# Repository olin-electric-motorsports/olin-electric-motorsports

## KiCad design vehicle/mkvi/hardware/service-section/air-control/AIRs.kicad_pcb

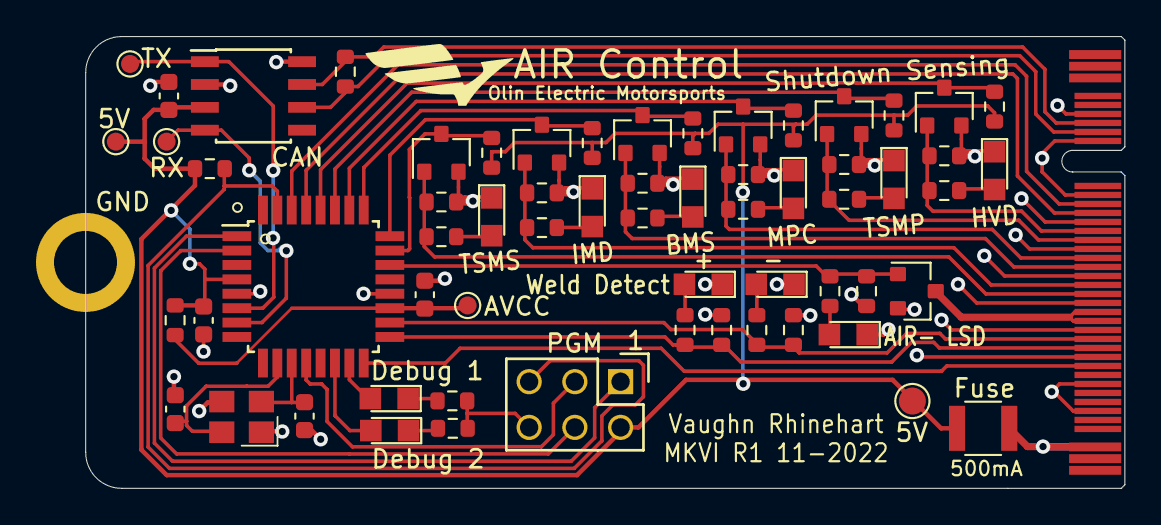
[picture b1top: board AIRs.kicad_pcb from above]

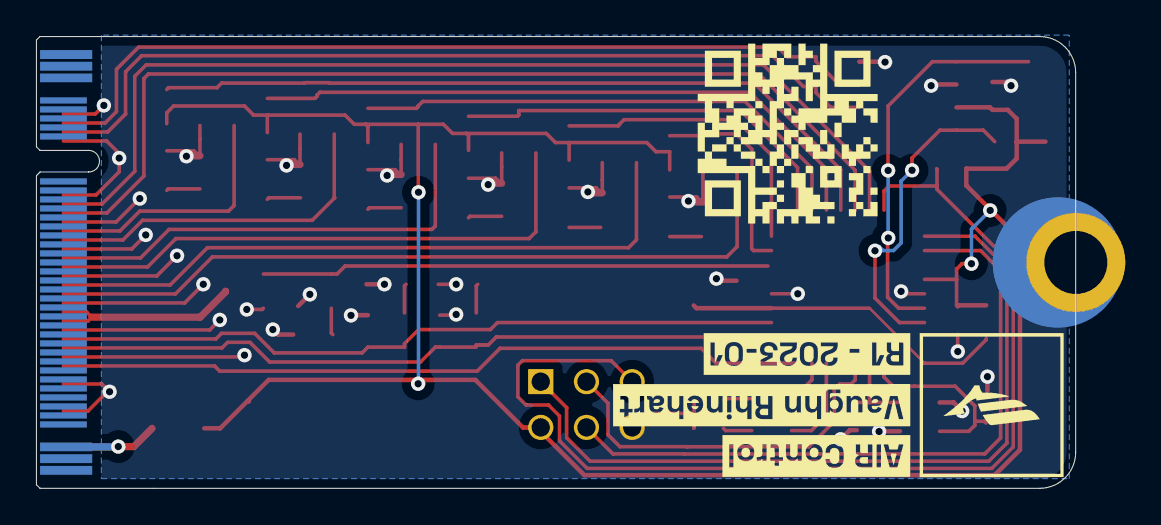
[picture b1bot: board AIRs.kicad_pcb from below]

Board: 2 copper layers, 57.7 x 25.1 mm, 68 parts (4 on the bottom side), 46 nets.

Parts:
C1, C7: 0.1uF; C_0603
C2: C_100pF; C_0603
C3, C4: C_30pF; C_0603
D2, D3, D4: LED_WHITE; CHIPLED_0805
D5, D6, D7, D8, D9, D10: LED_BLUE; CHIPLED_0805
F1: F_500mA_16V; Fuse_1210
J1: Programming; Pin_Header_Straight_2x03
J2: M.2 Edge Connector; Automotive_M.2_Edge_Connector
PD1, PD2: LED_WHITE; CHIPLED_0805
Q1, Q2, Q3, Q4, Q5, Q6, Q7: SSM3K333R; SOT-23F
QR*****: hw.oem.to/6_AIR-CNTL_1; QR_6_AIR-CNTL_1
R1: R_100; R_0603
R2, R3, R6, R7, R8: 1KR; R_0603
R4, R9, R10, R11, R12, R15, R18, R21, R24, R27: R_10K; R_0603
R13, R16, R19, R22, R25, R28: R_100K; R_0603
R14, R17, R20, R23, R26, R29: 3KR; R_0603
R30: R_120_DNP; R_0603
TP1, TP2, TP3, TP4: Test_Point_SMD; TestPoint_Pad_D1.0mm
TP5: Test_Point_SMD; TestPoint_Pad_D1.5mm
TP7: Test_Point_SMD; M.2_Mount
U1: ATMEGA16M1; TQFP-32_7x7mm_Pitch0.8mm
U2: MAX33011EASA; SOIC-8_3.9x4.9mm_Pitch1.27mm_OEM
Y1: Crystal_16MHz_18pF; Crystal_TXC7M
kibuzzard-63BF4696: G***; kibuzzard-63BF4696
kibuzzard-63D83D19: G***; kibuzzard-63D83D19
kibuzzard-63D83D27: G***; kibuzzard-63D83D27

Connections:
+5V: C1.1, C7.1, F1.1, J1.2, R1.1, R4.2, R12.1, R15.1, R18.1, R21.1, R24.1, R27.1, TP1.1, TP5.1, U1.4 (VCC), U2.3 (VDD)
/AIR+_WELD_DETECT: J2.28, R6.1, R9.1, U1.17 ((PCINT12/ADC8/ACMPN3/AMP1-)PC4)
/AIR-_LSD: Q1.1 (G), R7.1, R10.1, U1.22 ((PCINT14/ADC10/ACMP1)PC6)
/AIR-_LSD_OUT: J2.24, J2.25, Q1.3 (D)
/AIR-_WELD_DETECT: J2.27, R8.1, R11.1, U1.18 ((PCINT13/ADC9/ACMP3/AMP1+)PC5)
/CAN Tcvr./CAN RX: TP4.1, U1.7 ((PCINT11/T1/ICP1B/RXCAN)PC3), U2.4 (RXD)
/CAN Tcvr./CAN TX: TP3.1, U1.6 ((PCINT10/T0/TXCAN)PC2), U2.1 (TXD)
/CAN_+: J2.7, R30.1, U2.7 (CANH)
/CAN_-: J2.8, R30.2, U2.6 (CANL)
/IMD_PWM: J2.12, U1.30 ((PCINT8/INT3/PSCOUT1A)PC0)
/IMD_STATUS: J2.13, U1.29 ((PCINT16/PSCOUT0A)PD0)
/MISO: J1.1, U1.1 ((PCINT18/PSCIN2/OC1A/MISO_A)PD2)
/MOSI: J1.4, U1.2 ((PCINT19/TXD/TXLIN/OC0A/~SS/MOSI_A)PD3)
/PRECHARGE: J2.30, U1.16 ((PCINT2/ADC5/INT1/ACMPN0)PB2)
/RESET: J1.5, R4.1, U1.31 ((PCINT24/OCD/~RESET)PE0)
/SCK: J1.3, U1.12 ((PCINT20/ADC1/RXD/RXLIN/ICP1A/SCK_A)PD4)
/SHDN_SENSE_BMS: Q5.3 (D), R21.2, U1.25 ((PCINT15/D2A/AMP2+)PC7)
/SHDN_SENSE_BMS_12V: J2.19, Q5.1 (G), R22.1, R23.1
/SHDN_SENSE_HVD: Q2.3 (D), R12.2, U1.28 ((PCINT7/ADC4/SCK/PSCOUT0B)PB7)
/SHDN_SENSE_HVD_12V: J2.15, Q2.1 (G), R13.1, R14.1
/SHDN_SENSE_IMD: Q6.3 (D), R24.2, U1.24 ((PCINT4/AMP0+)PB4)
/SHDN_SENSE_IMD_12V: J2.21, Q6.1 (G), R25.1, R26.1
/SHDN_SENSE_MPC: Q4.3 (D), R18.2, U1.26 ((PCINT5/ADC6/INT2/ACMPN1/AMP2-)PB5)
/SHDN_SENSE_MPC_12V: J2.18, Q4.1 (G), R19.1, R20.1
/SHDN_SENSE_TSMP: Q3.3 (D), R15.2, U1.27 ((PCINT6/ADC7/PSCOUT1B)PB6)
/SHDN_SENSE_TSMP_12V: J2.16, Q3.1 (G), R16.1, R17.1
/SHDN_SENSE_TSMS: Q7.3 (D), R27.2, U1.23 ((PCINT3/AMP0-)PB3)
/SHDN_SENSE_TSMS_12V: J2.22, Q7.1 (G), R28.1, R29.1
GND: C1.2, C2.2, C3.2, C4.2, C7.2, D2.1 (K), D3.1 (K), D4.1 (K), D5.1 (K), D6.1 (K), D7.1 (K), D8.1 (K), D9.1 (K), D10.1 (K), J1.6, J2.6, J2.9, J2.11, J2.14, J2.17, J2.20, J2.23, J2.26, J2.29, J2.32, J2.35, Q1.2 (S), Q2.2 (S), Q3.2 (S), Q4.2 (S), Q5.2 (S), Q6.2 (S), Q7.2 (S), R2.2, R3.2, R9.2, R10.2, R11.2, R13.2, R16.2, R19.2, R22.2, R25.2, R28.2, TP7.1, U1.5 (GND), U1.20 (AGND), U2.2 (VSS), U2.8 (STBY), Y1.2, Y1.4
unnamed: C2.1, R1.2, TP2.1, U1.19 (AVCC)
unnamed: C3.1, U1.11 ((PCINT26/ADC0/XTAL2)PE2), Y1.1
unnamed: C4.1, U1.10 ((PCINT25/OC0B/XTAL1)PE1), Y1.3
unnamed: D2.2 (A), R6.2
unnamed: D3.2 (A), R7.2
unnamed: D4.2 (A), R8.2
unnamed: D5.2 (A), R14.2
unnamed: D6.2 (A), R17.2
unnamed: D7.2 (A), R20.2
unnamed: D8.2 (A), R23.2
unnamed: D9.2 (A), R26.2
unnamed: D10.2 (A), R29.2
unnamed: F1.2, J2.P38
unnamed: PD1.1 (K), R2.1
unnamed: PD1.2 (A), U1.14 ((PCINT22/ADC3/INT0/ACMPN2)PD6)
unnamed: PD2.1 (K), R3.1
unnamed: PD2.2 (A), U1.15 ((PCINT23/ACMP0)PD7)

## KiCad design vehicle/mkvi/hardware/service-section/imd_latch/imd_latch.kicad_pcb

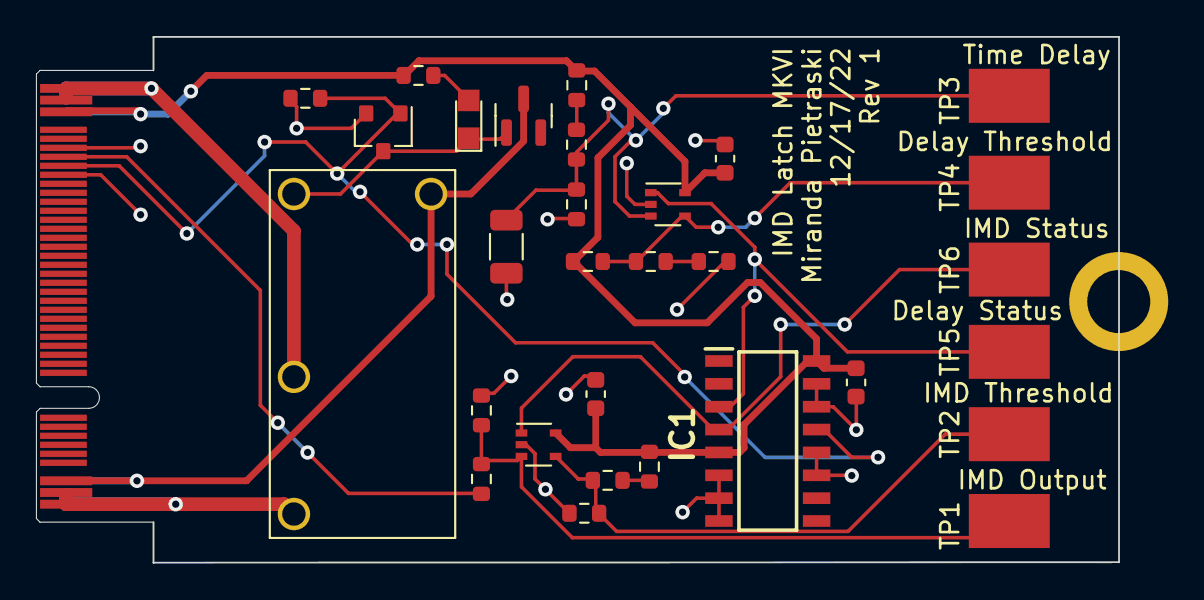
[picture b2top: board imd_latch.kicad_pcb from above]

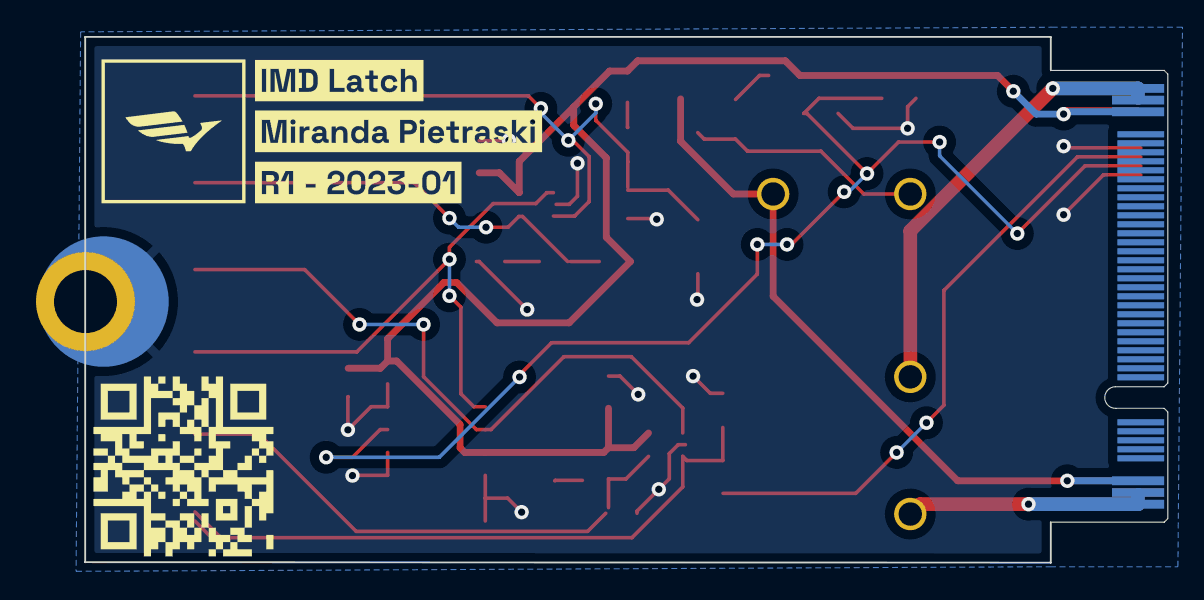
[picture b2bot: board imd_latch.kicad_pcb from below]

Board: 2 copper layers, 60.1 x 29.2 mm, 36 parts (4 on the bottom side), 18 nets.

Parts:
C1: C_22uF; C_1206_3216Metric
C2, C3, C4: 0.1uF; C_0603
D1: BAS40; SOT-23
D2: LED_WHITE; CHIPLED_0805
H1: M.2_MountingHole; M.2_Mount
IC1: CD4044BDR; SOIC127P600X175-16N
J2: Automotive_M.2_Edge_Connector
K1: G5Q-1A4-DC12; Relay_SPST_OMRON-G5Q-1A4_OEM
Q1: SSM3K333R; SOT-23F
QR*****: hw.oem.to/6_IMD-LATCH_1; QR_6_IMD-LATCH_1
R1, R3, R4, R6, R7, R11: R_100K; R_0603
R2: R_71.5k; R_0603
R5: R_120K; R_0603
R8: R_3K; R_0603
R9, R13: R_1K; R_0603
R10: R_1.82M; R_0603
R12: R_604K; R_0603
TP1, TP2, TP3, TP4, TP5, TP6: Test_Point_SMD
U1, U2: MCP6001; SOT-353_SC-70-5
kibuzzard-63BF4696: G***; kibuzzard-63BF4696
kibuzzard-63D83E83: G***; kibuzzard-63D83E83
kibuzzard-63D83E95: G***; kibuzzard-63D83E95

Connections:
+5V: C2.1, C3.1, C4.1, IC1.5 (ENABLE), IC1.16 (VDD), J2.P38, R1.1, R2.2, R3.1, R13.1, U1.5 (V+), U2.5 (V+)
+BATT: D1.3 (K), J2.P3, K1.5
/IMD_OUTPUT: J2.34, R8.1
/IMD_STATUS: IC1.13 (Q1), J2.33, Q1.1 (G), R12.1
/IMD_STATUS_OUTPUT: IC1.4 (RI), TP6.1, U1.1
/SHDN_IN: J2.P1, J2.P2, K1.3
/SHDN_OUT: J2.P39, J2.P40, K1.2
/TIME_DELAY: IC1.3 (SI), TP5.1, U2.1
GND: C1.2, C2.2, C3.2, C4.2, H1.1, IC1.6 (R2), IC1.7 (S2), IC1.8 (VSS), IC1.11 (S3), IC1.12 (R3), IC1.14 (R4), IC1.15 (S4), J2.32, J2.35, Q1.2 (S), R6.1, R7.1, R9.2, R10.2, R12.2, U1.2 (V-), U2.2 (V-)
unnamed: C1.1, R5.2, R10.1, TP3.1, U2.3 (+)
unnamed: D1.1 (A), D2.1 (K), K1.1, Q1.3 (D)
unnamed: D2.2 (A), R13.2
unnamed: R1.2, R4.2, TP4.1, U2.4 (-)
unnamed: R2.1, R5.1
unnamed: R4.1, R7.2
unnamed: R8.2, R9.1, TP1.1, U1.3 (+)
unnamed: R3.2, R11.1
unnamed: R6.2, R11.2, TP2.1, U1.4 (-)

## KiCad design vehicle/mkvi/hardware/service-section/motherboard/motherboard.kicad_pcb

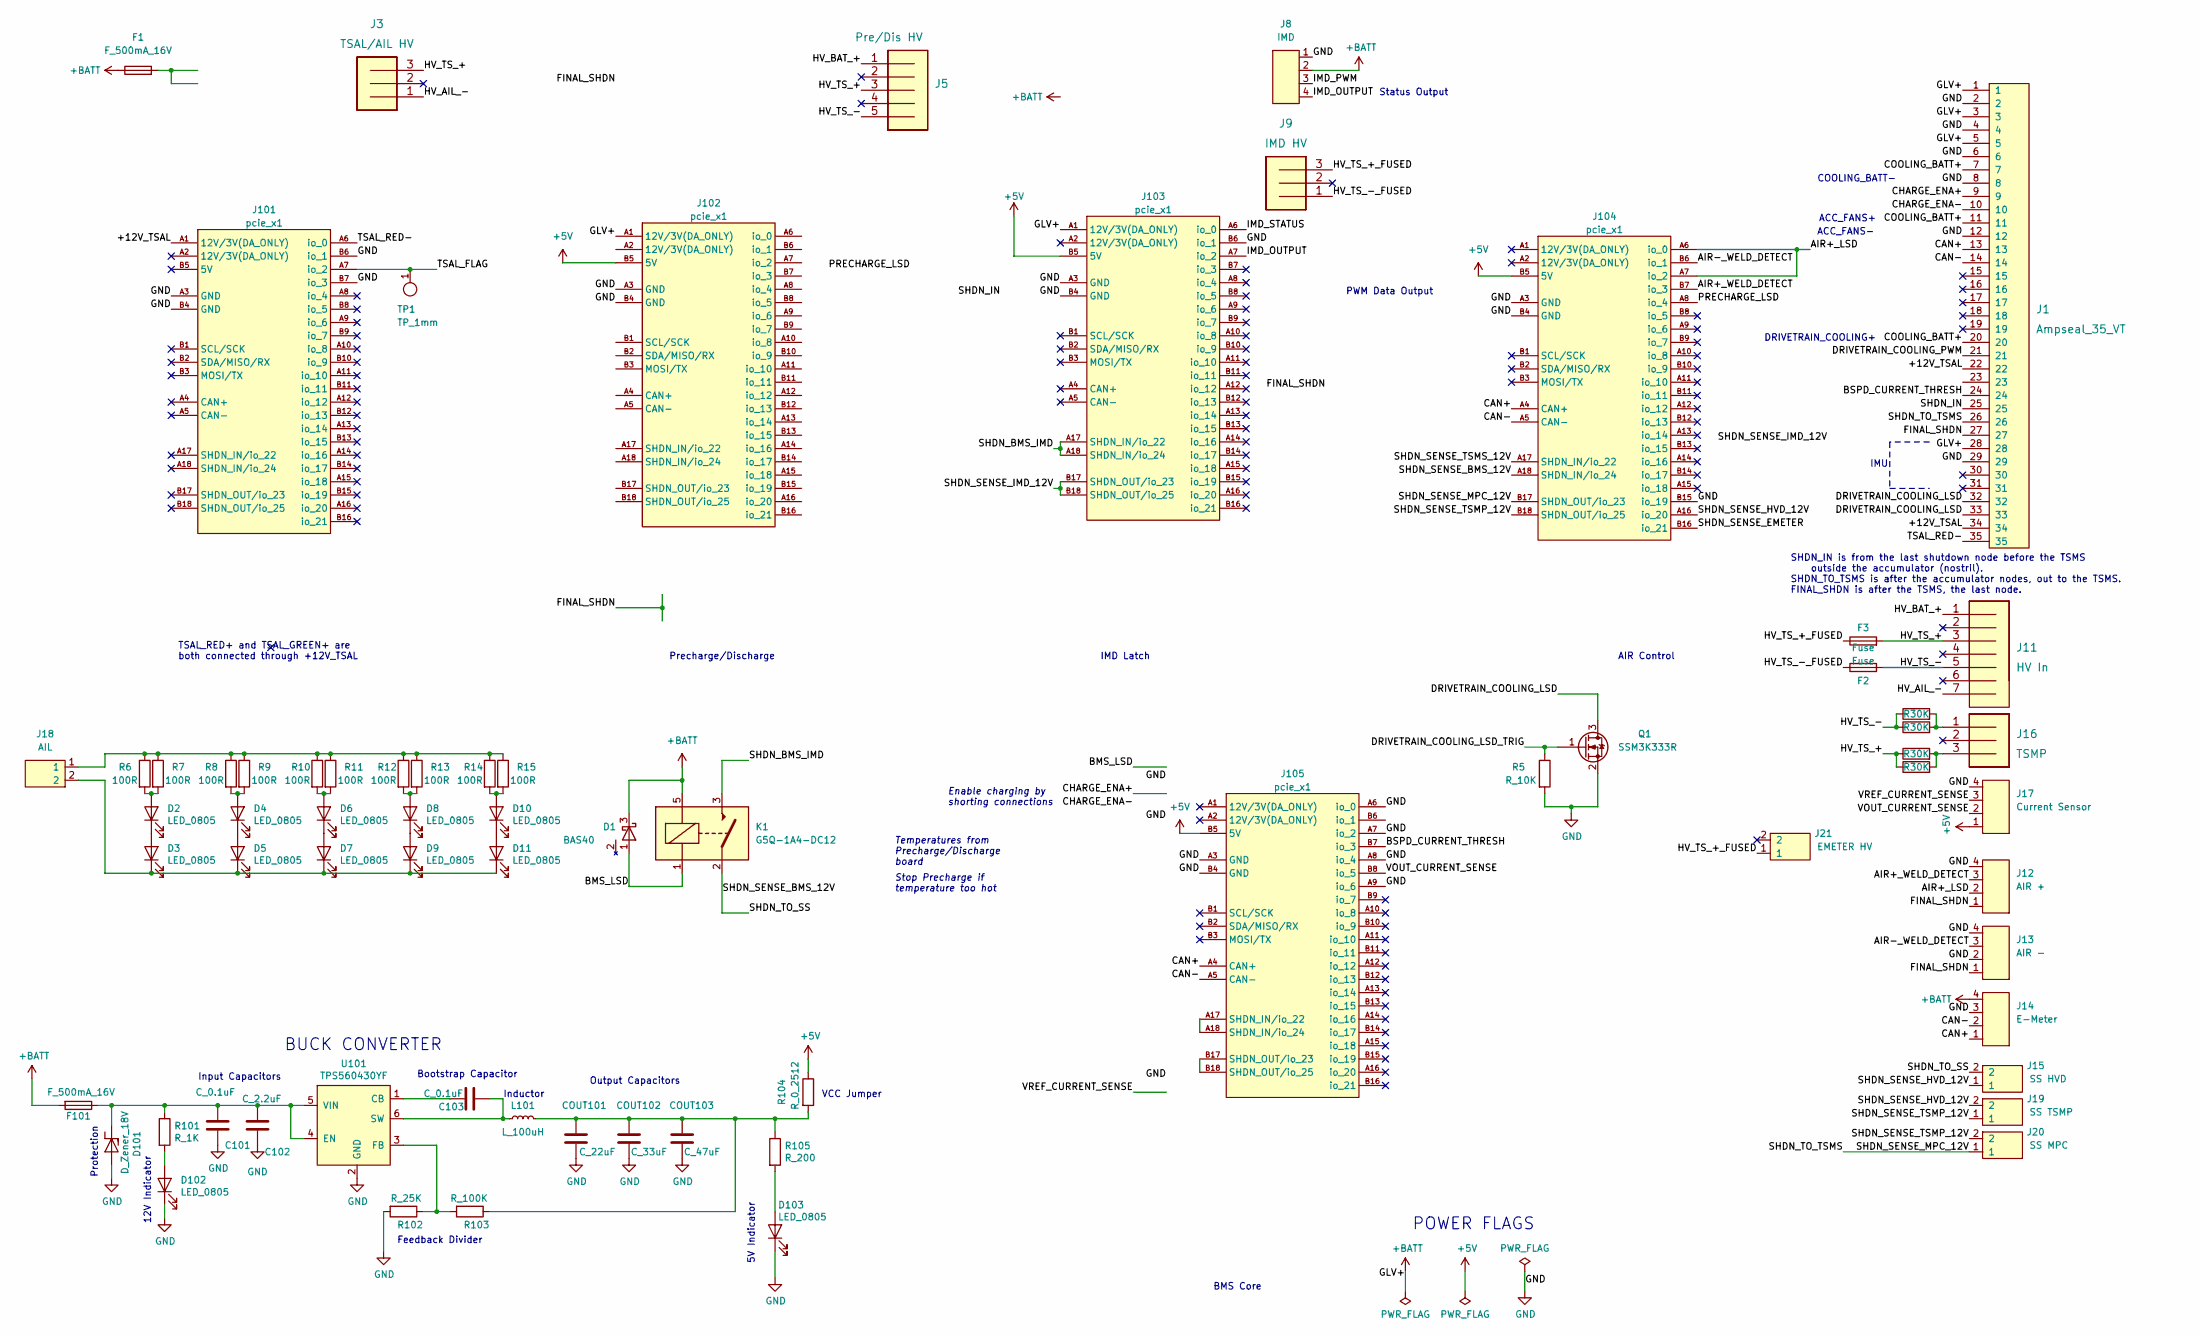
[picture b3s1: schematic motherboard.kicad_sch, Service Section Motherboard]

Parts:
C101, C103: C_0.1uF; C_0805_OEM; MPN 478-3352-1-ND
C102: C_2.2uF; C_0603_1608Metric; MPN 311-1451-1-ND
COUT101: C_22uF; C_1206_OEM; MPN 445-11693-1-ND
COUT102: C_33uF; Fuse_1812; MPN 445-3924-1-ND
COUT103: C_47uF; C_0805_OEM; MPN 1276-6467-1-ND
D1: BAS40; SOT-23; MPN BAS40
D2, D3, D4, D5, D6, D7, D8, D9, D10, D11: LED_0805; LED_0805_OEM_no_border; MPN 475-1410-1-ND
D101: D_Zener_18V; DO-214AA; MPN SMBJ5355B-TPMSCT-ND
D102, D103: LED_0805; LED_0805_OEM; MPN 475-1410-1-ND
F1: F_500mA_16V; Fuse_1210; MPN 0ZCH0050FF2G
F2, F3: Fuse; 4245_fuse_holder
F101: F_500mA_16V; Fuse_1210; MPN 507-1786-1-ND
J1: Ampseal_35_VT; Ampseal_35; MPN 1-776231-1
J3: TSAL/AIL HV; MicroFit_VT_3; MPN 436500327
J5: Pre/Dis HV; Connector_MicroFit_VT_5x1; MPN 436500515
J8: IMD; MicroFit_VT_4; MPN 430450414
J9: IMD HV; MicroFit_VT_3; MPN 436500327
J11: HV In; MicroFit_VT_7; MPN 436500727
J12: AIR +; MicroFit_VT_4; MPN 430450414
J13: AIR -; MicroFit_VT_4; MPN 430450414
J14: E-Meter; MicroFit_VT_4; MPN 430450414
J15: SS HVD; MicroFit_V_2; MPN WM10660-ND
J16: TSMP; MicroFit_VT_3; MPN 436500327
J17: Current Sensor; MicroFit_VT_4; MPN 430450414
J18: AIL; MicroFit_V_2; MPN WM10660-ND
J19: SS TSMP; MicroFit_V_2; MPN WM10660-ND
J20: SS MPC; MicroFit_V_2; MPN WM10660-ND
J21: EMETER HV; MicroFit_V_2; MPN WM10660-ND
J101, J102, J103, J104, J105: pcie_x1; te_pcie_x1_connector
K1: G5Q-1A4-DC12; Relay_SPST_OMRON-G5Q-1A4_OEM; MPN G5Q-1A4 DC12
L101: L_100uH; L_100uH_OEM; MPN 445-15759-1-ND
Q1: SSM3K333R; SOT-23F; MPN SSM3K333RLFCT-ND
R1, R2, R3, R4: R30K; R_TSMP_SMD_5329
R5: R_10K; R_0603; MPN RMCF0603FT10K0
R6, R7, R8, R9, R10, R11, R12, R13, R14, R15: 100R; R_0603; MPN RMCF0603FT100R
R101: R_1K; R_0805_OEM; MPN RNCP0805FTD1K00CT-ND
R102: R_25K; R_0805_OEM; Digi-key Part Number CPF-A-0805B25KE
R103: R_100K; R_0805_OEM; MPN P100KCCT-ND
R104: R_0_2512; R_2512_OEM; MPN A121322CT-ND
R105: R_200; R_0805_OEM; MPN RMCF0805JT200RCT-ND
TP1: TP_1mm; TestPoint_Pad_D1.0mm
U101: TPS560430YF; SOT-23-6_OEM; MPN TPS560430YFDBVR

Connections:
+5V: J17.1, R104.1; also elsewhere on the board
/+12V_TSAL: J1.22, J1.34, J101.A1 (12V/3V(DA_ONLY))
/AIR+_LSD: J12.2, J104.A6 (io_0), J104.A7 (io_2); also elsewhere on the board
/AIR+_WELD_DETECT: J12.3, J104.B7 (io_3); also elsewhere on the board
/AIR-_WELD_DETECT: J13.3, J104.B6 (io_1); also elsewhere on the board
/BMS_LSD: D1.1 (A), K1.1; also elsewhere on the board
/CAN+: J1.13, J1.15, J1.17, J1.30, J14.1, J104.A4 (CAN+), J105.A4 (CAN+); also elsewhere on the board
/CAN-: J1.14, J1.16, J1.18, J1.31, J14.2, J104.A5 (CAN-), J105.A5 (CAN-); also elsewhere on the board
/CHARGE_ENA+: J1.9; also elsewhere on the board
/CHARGE_ENA-: J1.10; also elsewhere on the board
/COOLING_BATT+: J1.7, J1.11, J1.20
/DRIVETRAIN_COOLING_LSD: J1.32, J1.33, Q1.3 (D)
/DRIVETRAIN_COOLING_LSD_TRIG: Q1.1 (G), R5.1; also elsewhere on the board
/DRIVETRAIN_COOLING_PWM: J1.21; also elsewhere on the board
/FINAL_SHDN: J1.27, J12.1, J13.1; also elsewhere on the board
/HV_AIL_-: J3.1, J11.7
/HV_BAT_+: J5.1, J11.1
/HV_TS_+: F3.2, J3.3, J5.3, J11.3, R2.1, R4.1
/HV_TS_+_FUSED: F3.1, J9.3, J21.1
/HV_TS_-: F2.2, J5.5, J11.5, R1.1, R3.1
/HV_TS_-_FUSED: F2.1, J9.1
/IMD_OUTPUT: J8.4, J103.A7 (io_2); also elsewhere on the board
/IMD_PWM: J8.3; also elsewhere on the board
/I_SENSE_BSPD: J1.24, J105.B7 (io_3); also elsewhere on the board
/SHDN_BMS_IMD: J103.A17 (SHDN_IN/io_22), J103.A18 (SHDN_IN/io_24), K1.3; also elsewhere on the board
/SHDN_IN: J1.25; also elsewhere on the board
/SHDN_SENSE_BMS_12V: J15.2, J104.A18 (SHDN_IN/io_24), K1.2; also elsewhere on the board
/SHDN_SENSE_HVD_12V: J15.1, J19.2, J104.A16 (io_20); also elsewhere on the board
/SHDN_SENSE_MPC_12V: J1.26, J20.1, J104.B17 (SHDN_OUT/io_23); also elsewhere on the board
/SHDN_SENSE_TSMP_12V: J19.1, J20.2, J104.B18 (SHDN_OUT/io_25); also elsewhere on the board
/TSAL_FLAG: J101.A7 (io_2), TP1.1; also elsewhere on the board
/TSAL_GREEN-: J1.23; also elsewhere on the board
/TSAL_RED-: J1.35, J101.A6 (io_0); also elsewhere on the board
/VOUT_CURRENT_SENSE: J17.2, J105.B8 (io_5); also elsewhere on the board
/VREF_CURRENT_SENSE: J17.3; also elsewhere on the board
unnamed: C101.1, C102.1, D101.1 (K), F101.1, R101.1, U101.4 (EN), U101.5 (VIN)
unnamed: C103.1, U101.1 (CB)
unnamed: C103.2, L101.1, U101.6 (SW)
unnamed: COUT101.1, COUT102.1, COUT103.1, L101.2, R103.1, R104.2, R105.1
unnamed: D2.1 (K), D3.2 (A)
unnamed: D2.2 (A), R6.2, R7.2
unnamed: D4.1 (K), D5.2 (A)
unnamed: D4.2 (A), R8.2, R9.2
unnamed: D6.1 (K), D7.2 (A)
unnamed: D6.2 (A), R10.2, R11.2
unnamed: D8.1 (K), D9.2 (A)
unnamed: D8.2 (A), R12.2, R13.2
unnamed: D10.1 (K), D11.2 (A)
unnamed: D10.2 (A), R14.2, R15.2
unnamed: D3.1 (K), D5.1 (K), D7.1 (K), D9.1 (K), D11.1 (K), J18.2
unnamed: D102.2 (A), R101.2
unnamed: D103.2 (A), R105.2
unnamed 57: F1.2; also elsewhere on the board
unnamed: J16.1, R1.2, R3.2
unnamed: J16.3, R2.2, R4.2
unnamed: J18.1, R6.1, R7.1, R8.1, R9.1, R10.1, R11.1, R12.1, R13.1, R14.1, R15.1
unnamed: J103.B5 (5V), J105.B5 (5V)
unnamed: J103.B17 (SHDN_OUT/io_23), J103.B18 (SHDN_OUT/io_25)
unnamed: J105.A17 (SHDN_IN/io_22), J105.A18 (SHDN_IN/io_24)
unnamed: J105.B17 (SHDN_OUT/io_23), J105.B18 (SHDN_OUT/io_25)
unnamed: R102.1, R103.2, U101.3 (FB)

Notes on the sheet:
AIR Control
DRIVETRAIN_COOLING+
Protection
BUCK CONVERTER
ACC_FANS+
ACC_FANS-
Stop Precharge if temperature too hot
Bootstrap Capacitor
COOLING_BATT-
Status Output
Output Capacitors
PWM Data Output
POWER FLAGS
12V Indicator
Input Capacitors
VCC Jumper
TSAL_RED+ and TSAL_GREEN+ are both connected through +12V_TSAL
Temperatures from Precharge/Discharge board
5V Indicator
Inductor
Feedback Divider
IMD Latch
Precharge/Discharge
BMS Core
SHDN_IN is from the last shutdown node before the TSMS outside the accumulator (nostril). SHDN_TO_TSMS is after the accumulator nodes, out to the TSMS. FINAL_SHDN is after the TSMS, the last node.
Enable charging by shorting connections
IMU

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
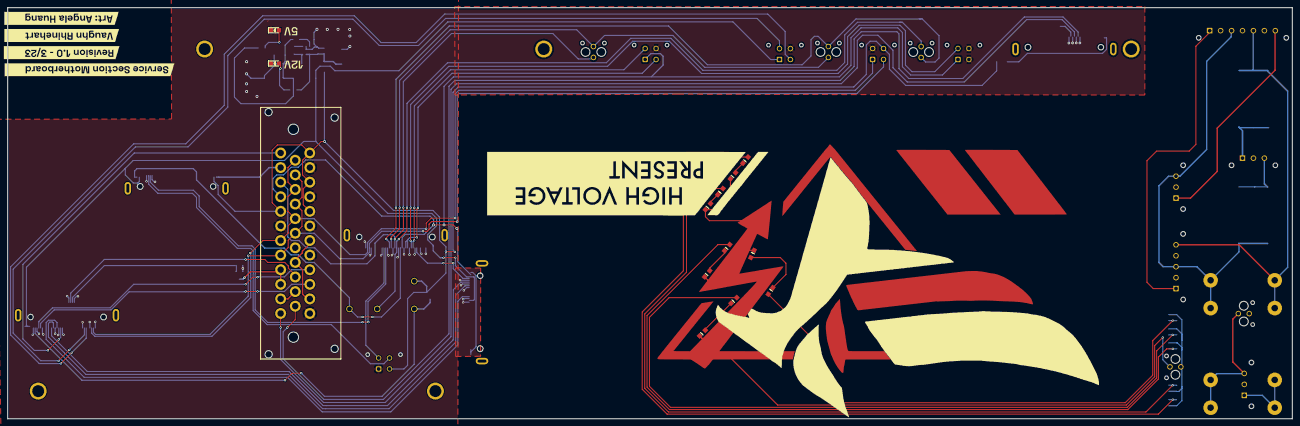
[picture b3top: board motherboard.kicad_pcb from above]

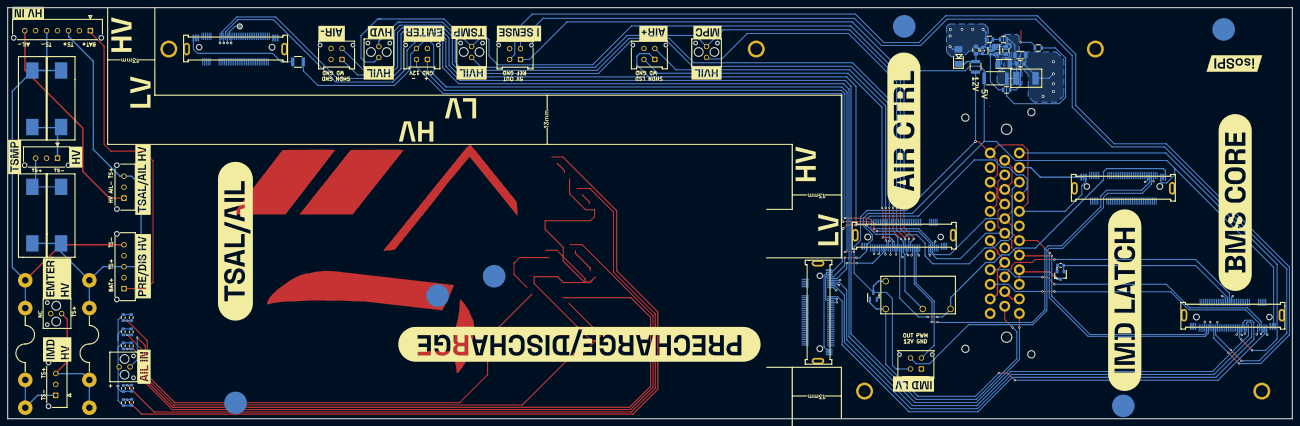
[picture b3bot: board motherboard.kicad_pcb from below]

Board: 2 copper layers, 352.2 x 112.7 mm, 111 parts (92 on the bottom side), 64 nets.

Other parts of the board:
J2: TSAL/AIL; MKVI_TSAL_AIL
J4: Precharge/Discharge; MKVI_PRECHARGE_DISCHARGE
J6: IMD Latch; MKVI_IMD_LATCH
J7: BMS Core; MKVI_BMS_CORE
J10: AIR Control; MKVI_AIR_CONTROL
kibuzzard-640A9A12: G***; kibuzzard-640A9A12
kibuzzard-640A9C0D: G***; kibuzzard-640A9C0D
kibuzzard-640A9CEC, kibuzzard-640A9CEC#2, kibuzzard-640A9CEC#3, kibuzzard-640A9CEC#4: G***; kibuzzard-640A9CEC
kibuzzard-640A99E6: G***; kibuzzard-640A99E6
kibuzzard-640A993C: G***; kibuzzard-640A993C
kibuzzard-640B8A64: G***; kibuzzard-640B8A64
kibuzzard-640B8A86: G***; kibuzzard-640B8A86
kibuzzard-640B8A91: G***; kibuzzard-640B8A91
kibuzzard-640B8AF3, kibuzzard-640B8AF3#2, kibuzzard-640B8AF3#3: G***; kibuzzard-640B8AF3
kibuzzard-640B8B5E: G***; kibuzzard-640B8B5E
kibuzzard-640B75B2, kibuzzard-640B75B2#2, kibuzzard-640B75B2#3: G***; kibuzzard-640B75B2
kibuzzard-640B76B0, kibuzzard-640B76B0#2, kibuzzard-640B76B0#3: G***; kibuzzard-640B76B0
kibuzzard-640B80AC: G***; kibuzzard-640B80AC
kibuzzard-640B83C1: G***; kibuzzard-640B83C1
kibuzzard-640B86B7: G***; kibuzzard-640B86B7
kibuzzard-640B87CD: G***; kibuzzard-640B87CD
kibuzzard-640B88BC: G***; kibuzzard-640B88BC
kibuzzard-640B88EE: G***; kibuzzard-640B88EE
kibuzzard-640B795F: G***; kibuzzard-640B795F
kibuzzard-640B861F: G***; kibuzzard-640B861F
kibuzzard-640B875E: G***; kibuzzard-640B875E
kibuzzard-640B888E: G***; kibuzzard-640B888E
kibuzzard-640B7958: G***; kibuzzard-640B7958
kibuzzard-640B7976: G***; kibuzzard-640B7976
kibuzzard-640B8282: G***; kibuzzard-640B8282
kibuzzard-640B8331: G***; kibuzzard-640B8331
kibuzzard-640B8404: G***; kibuzzard-640B8404
kibuzzard-640B8645: G***; kibuzzard-640B8645
kibuzzard-640B8668: G***; kibuzzard-640B8668
kibuzzard-640B8680: G***; kibuzzard-640B8680
kibuzzard-640B8767: G***; kibuzzard-640B8767
kibuzzard-640B8928: G***; kibuzzard-640B8928

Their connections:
+5V: J4.12, J6.P38, J7.P1, J7.P2, J7.P3, J10.P38; also elsewhere on the board
/AIR+_LSD: J10.24, J10.25; also elsewhere on the board
/AIR+_WELD_DETECT: J10.28; also elsewhere on the board
/AIR-_WELD_DETECT: J10.27; also elsewhere on the board
/BMS_LSD: J7.5; also elsewhere on the board
/CAN+: J7.32, J10.7; also elsewhere on the board
/CAN-: J7.33, J10.8; also elsewhere on the board
/CHARGE_ENA+: J7.7; also elsewhere on the board
/CHARGE_ENA-: J7.8; also elsewhere on the board
/DRIVETRAIN_COOLING_LSD_TRIG: J7.58; also elsewhere on the board
/DRIVETRAIN_COOLING_PWM: J7.57; also elsewhere on the board
/FINAL_SHDN: J4.P1, J4.P2, J4.P3, J4.P38, J4.P39, J4.P40, J10.22; also elsewhere on the board
/IMD_OUTPUT: J6.34; also elsewhere on the board
/IMD_PWM: J10.12; also elsewhere on the board
/IMD_STATUS: J6.33, J10.13
/I_SENSE_BSPD: J7.15; also elsewhere on the board
/PRECHARGE_LSD: J4.4, J10.30
/SHDN_BMS_IMD: J6.P39, J6.P40, J10.21; also elsewhere on the board
/SHDN_IN: J6.P1, J6.P2; also elsewhere on the board
/SHDN_SENSE_BMS_12V: J10.19; also elsewhere on the board
/SHDN_SENSE_HVD_12V: J10.15; also elsewhere on the board
/SHDN_SENSE_MPC_12V: J10.18; also elsewhere on the board
/SHDN_SENSE_TSMP_12V: J10.16; also elsewhere on the board
/TEMP_SENSE_DISCHARGE: J4.10, J7.13
/TEMP_SENSE_PRECHARGE1: J4.8, J7.11
/TEMP_SENSE_PRECHARGE2: J4.6, J7.10
/TSAL_FLAG: J2.15; also elsewhere on the board
/TSAL_GREEN-: J2.11; also elsewhere on the board
/TSAL_RED-: J2.13; also elsewhere on the board
/VOUT_CURRENT_SENSE: J7.29; also elsewhere on the board
/VREF_CURRENT_SENSE: J7.28; also elsewhere on the board
unnamed 57: J2.P1, J2.P2; also elsewhere on the board

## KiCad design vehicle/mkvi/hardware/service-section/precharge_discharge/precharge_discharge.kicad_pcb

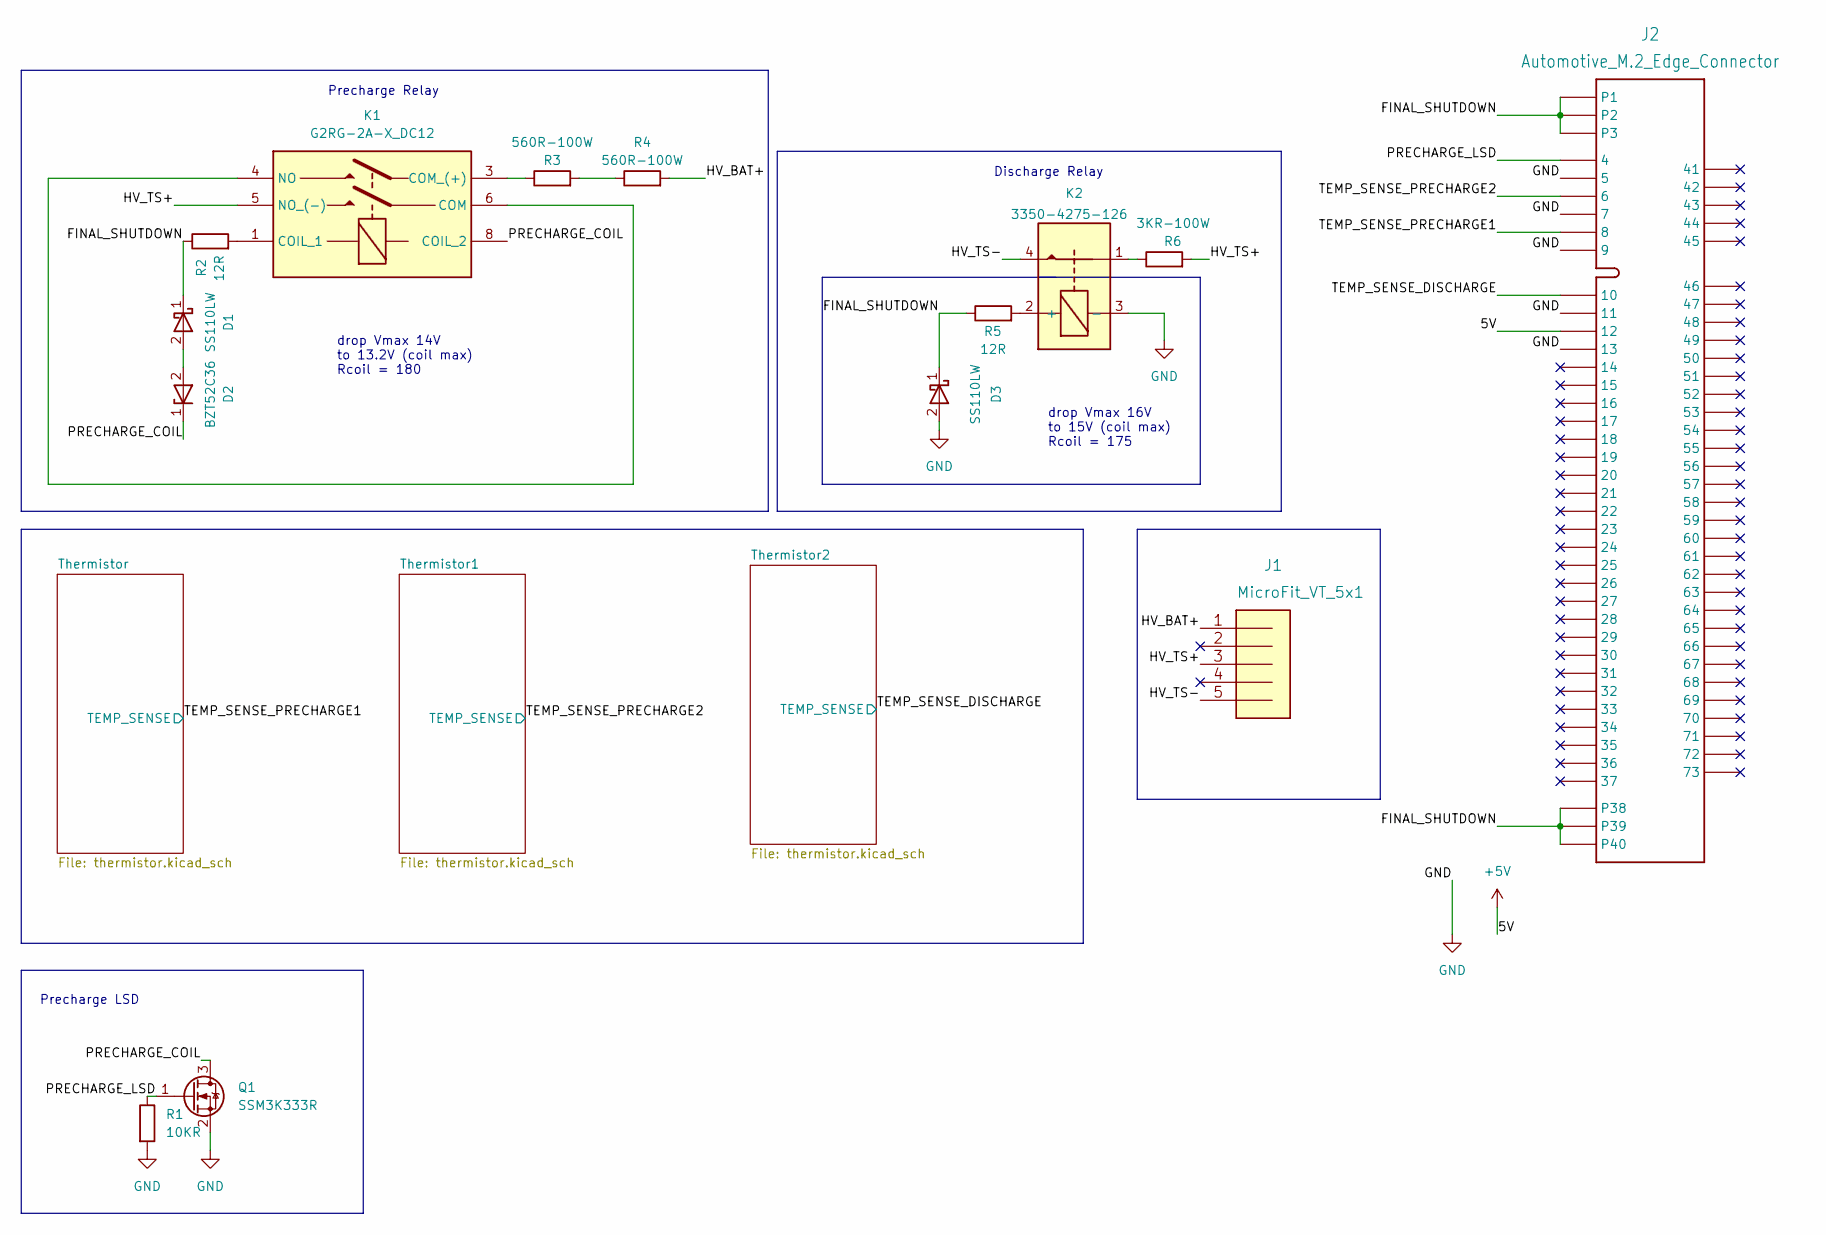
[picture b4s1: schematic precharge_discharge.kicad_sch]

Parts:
D1, D3: SS110LW; D_SOD-123; MPN SS110LW
D2: BZT52C36; D_SOD-123; MPN BZT52C36-7-F
J1: MicroFit_VT_5x1; Connector_MicroFit_VT_5x1; MPN 436500515
J2: Automotive_M.2_Edge_Connector; MPN N/A
K1: G2RG-2A-X_DC12; G2RG-X; MPN G2RG-2A-X DC12
K2: 3350-4275-126; Relay_Comus_3350; MPN 3350-4275-126
Q1: SSM3K333R; SOT-23F; MPN SSM3K333R,LF
R1: 10KR; R_0603; MPN RMCF0603FT10K0
R2, R5: 12R; R_0603; MPN RC0603FR-0712RL
R3, R4: 560R-100W; R_TO247-Heatsink; MPN AP101560RJ
R6: 3KR-100W; R_TO247-Heatsink; MPN AP1013KJ

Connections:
/FINAL_SHUTDOWN: D1.1 (K), D3.1 (K), J2.P1, J2.P2, J2.P3, J2.P38, J2.P39, J2.P40, R2.1, R5.1
/HV_BAT+: J1.1, R4.2
/HV_TS+: J1.3, K1.5 (NO_(-)), R6.2
/HV_TS-: J1.5, K2.4
/PRECHARGE_COIL: D2.1 (K), K1.8 (COIL_2), Q1.3 (D)
/PRECHARGE_LSD: J2.4, Q1.1 (G), R1.1
/TEMP_SENSE_DISCHARGE: J2.10; also elsewhere on the board
/TEMP_SENSE_PRECHARGE1: J2.8; also elsewhere on the board
/TEMP_SENSE_PRECHARGE2: J2.6; also elsewhere on the board
GND: D3.2 (A), J2.5, J2.7, J2.9, J2.11, J2.13, K2.3 (-), Q1.2 (S), R1.2; also elsewhere on the board
unnamed: D1.2 (A), D2.2 (A)
unnamed: K1.1 (COIL_1), R2.2
unnamed: K1.3 (COM_(+)), R3.1
unnamed: K1.4 (NO), K1.6 (COM)
unnamed: K2.1, R6.1
unnamed: K2.2 (+), R5.2
unnamed: R3.2, R4.1

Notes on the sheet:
drop Vmax 14V to 13.2V (coil max) Rcoil = 180
Discharge Relay
drop Vmax 16V to 15V (coil max) Rcoil = 175
Precharge LSD
Precharge Relay

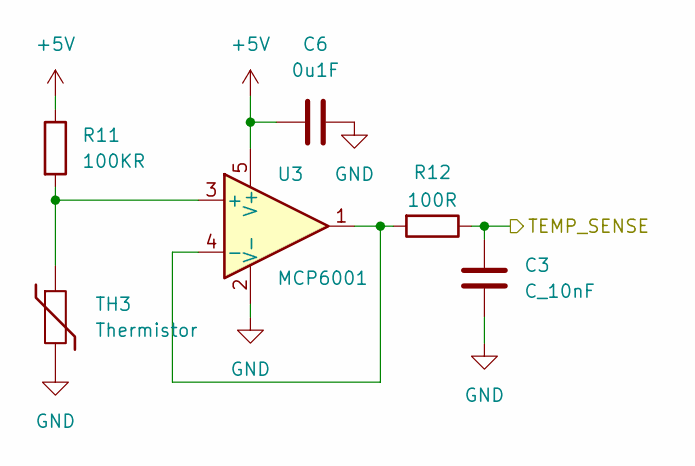
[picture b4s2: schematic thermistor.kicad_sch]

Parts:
C3: C_10nF; C_0603; MPN CL10B103KB8NNNC
C6: 0u1F; C_0603; MPN CL10B104KB8NNWC
R11: 100KR; R_0603; MPN RMCF0603FT100K
R12: 100R; R_0603; MPN RMCF0603FT100R
TH3: Thermistor
U3: MCP6001; SOT-353_SC-70-5; MPN MCP6001T-I/OT

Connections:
/TEMP_SENSE_PRECHARGE1: C3.1, R12.1; also elsewhere on the board
GND: C3.2, C6.2, TH3.2, U3.2 (V-); also elsewhere on the board
unnamed: R11.2, TH3.1, U3.3 (+)
unnamed: R12.2, U3.1, U3.4 (-)

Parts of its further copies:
C1, C2: C_10nF; C_0603; MPN CL10B103KB8NNNC
C4, C5: 0u1F; C_0603; MPN CL10B104KB8NNWC
R7, R9: 100KR; R_0603; MPN RMCF0603FT100K
R8, R10: 100R; R_0603; MPN RMCF0603FT100R
TH1, TH2: Thermistor
U1, U2: MCP6001; SOT-353_SC-70-5; MPN MCP6001T-I/OT

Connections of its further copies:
/TEMP_SENSE_DISCHARGE: C2.1, R10.1; also elsewhere on the board
/TEMP_SENSE_PRECHARGE2: C1.1, R8.1; also elsewhere on the board
GND: C1.2, C2.2, C4.2, C5.2, TH1.2, TH2.2, U1.2 (V-), U2.2 (V-); also elsewhere on the board
unnamed: R7.2, TH1.1, U1.3 (+)
unnamed: R8.2, U1.1, U1.4 (-)
unnamed: R9.2, TH2.1, U2.3 (+)
unnamed: R10.2, U2.1, U2.4 (-)

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
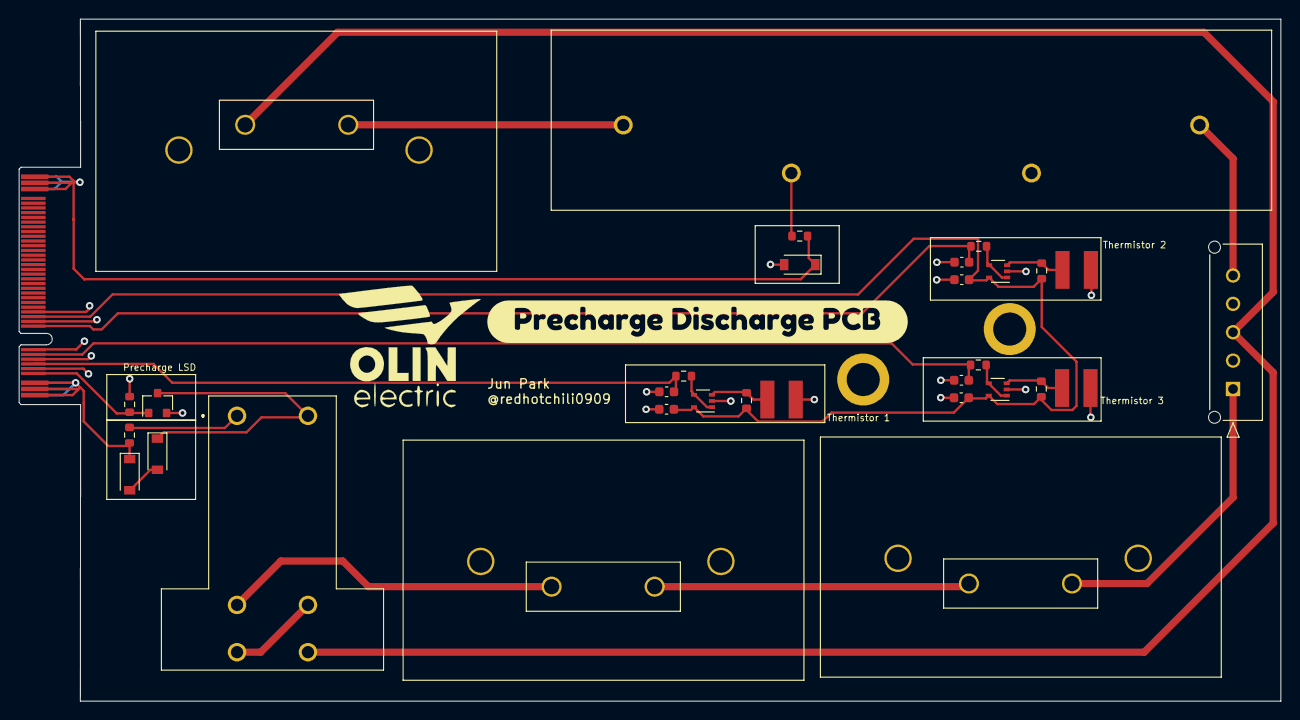
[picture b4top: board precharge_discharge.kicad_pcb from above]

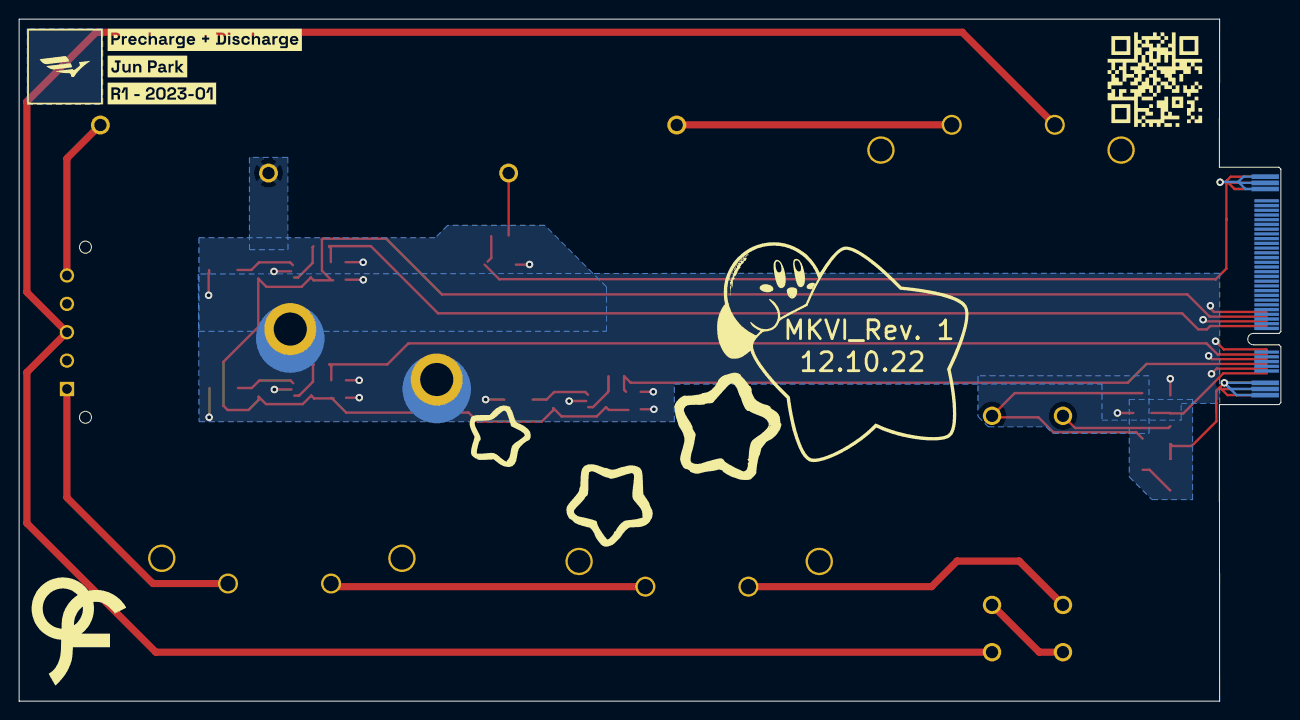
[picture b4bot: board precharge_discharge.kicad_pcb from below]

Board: 2 copper layers, 133.5 x 72.1 mm, 42 parts (7 on the bottom side), 24 nets.

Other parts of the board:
G1: LOGO; star
G2: LOGO; fromis
G3: LOGO; kirbystar2
QR*****: hw.oem.to/6_P-D-CHRG_1; QR_6_P-D-CHRG_1
U$2, U$2#2: M.2_Mount
kibuzzard-63BF4696: G***; kibuzzard-63BF4696
kibuzzard-63D840B7: G***; kibuzzard-63D840B7
kibuzzard-63D8409B: G***; kibuzzard-63D8409B
kibuzzard-639639B8: G***; kibuzzard-639639B8

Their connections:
GND: U$2.1, U$2#2.1; also elsewhere on the board

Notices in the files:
parts and their libraries:
Copyright 2021 Accelerated Designs. All rights reserved.
